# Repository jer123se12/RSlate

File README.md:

# RSlate
A 40key acrylic stack keyboard that is either hotswap with low profile switches or normal one but not hotswap.
Supports Vial
Currently Done!
---
|||
|---|---|
|Front|Back|
---
3d files are at [here](https://cad.onshape.com/documents/8e13d1f4745863165f092818/w/d03652fcd09787199e2b8651/e/c43cd68ad85962de6582dd97)

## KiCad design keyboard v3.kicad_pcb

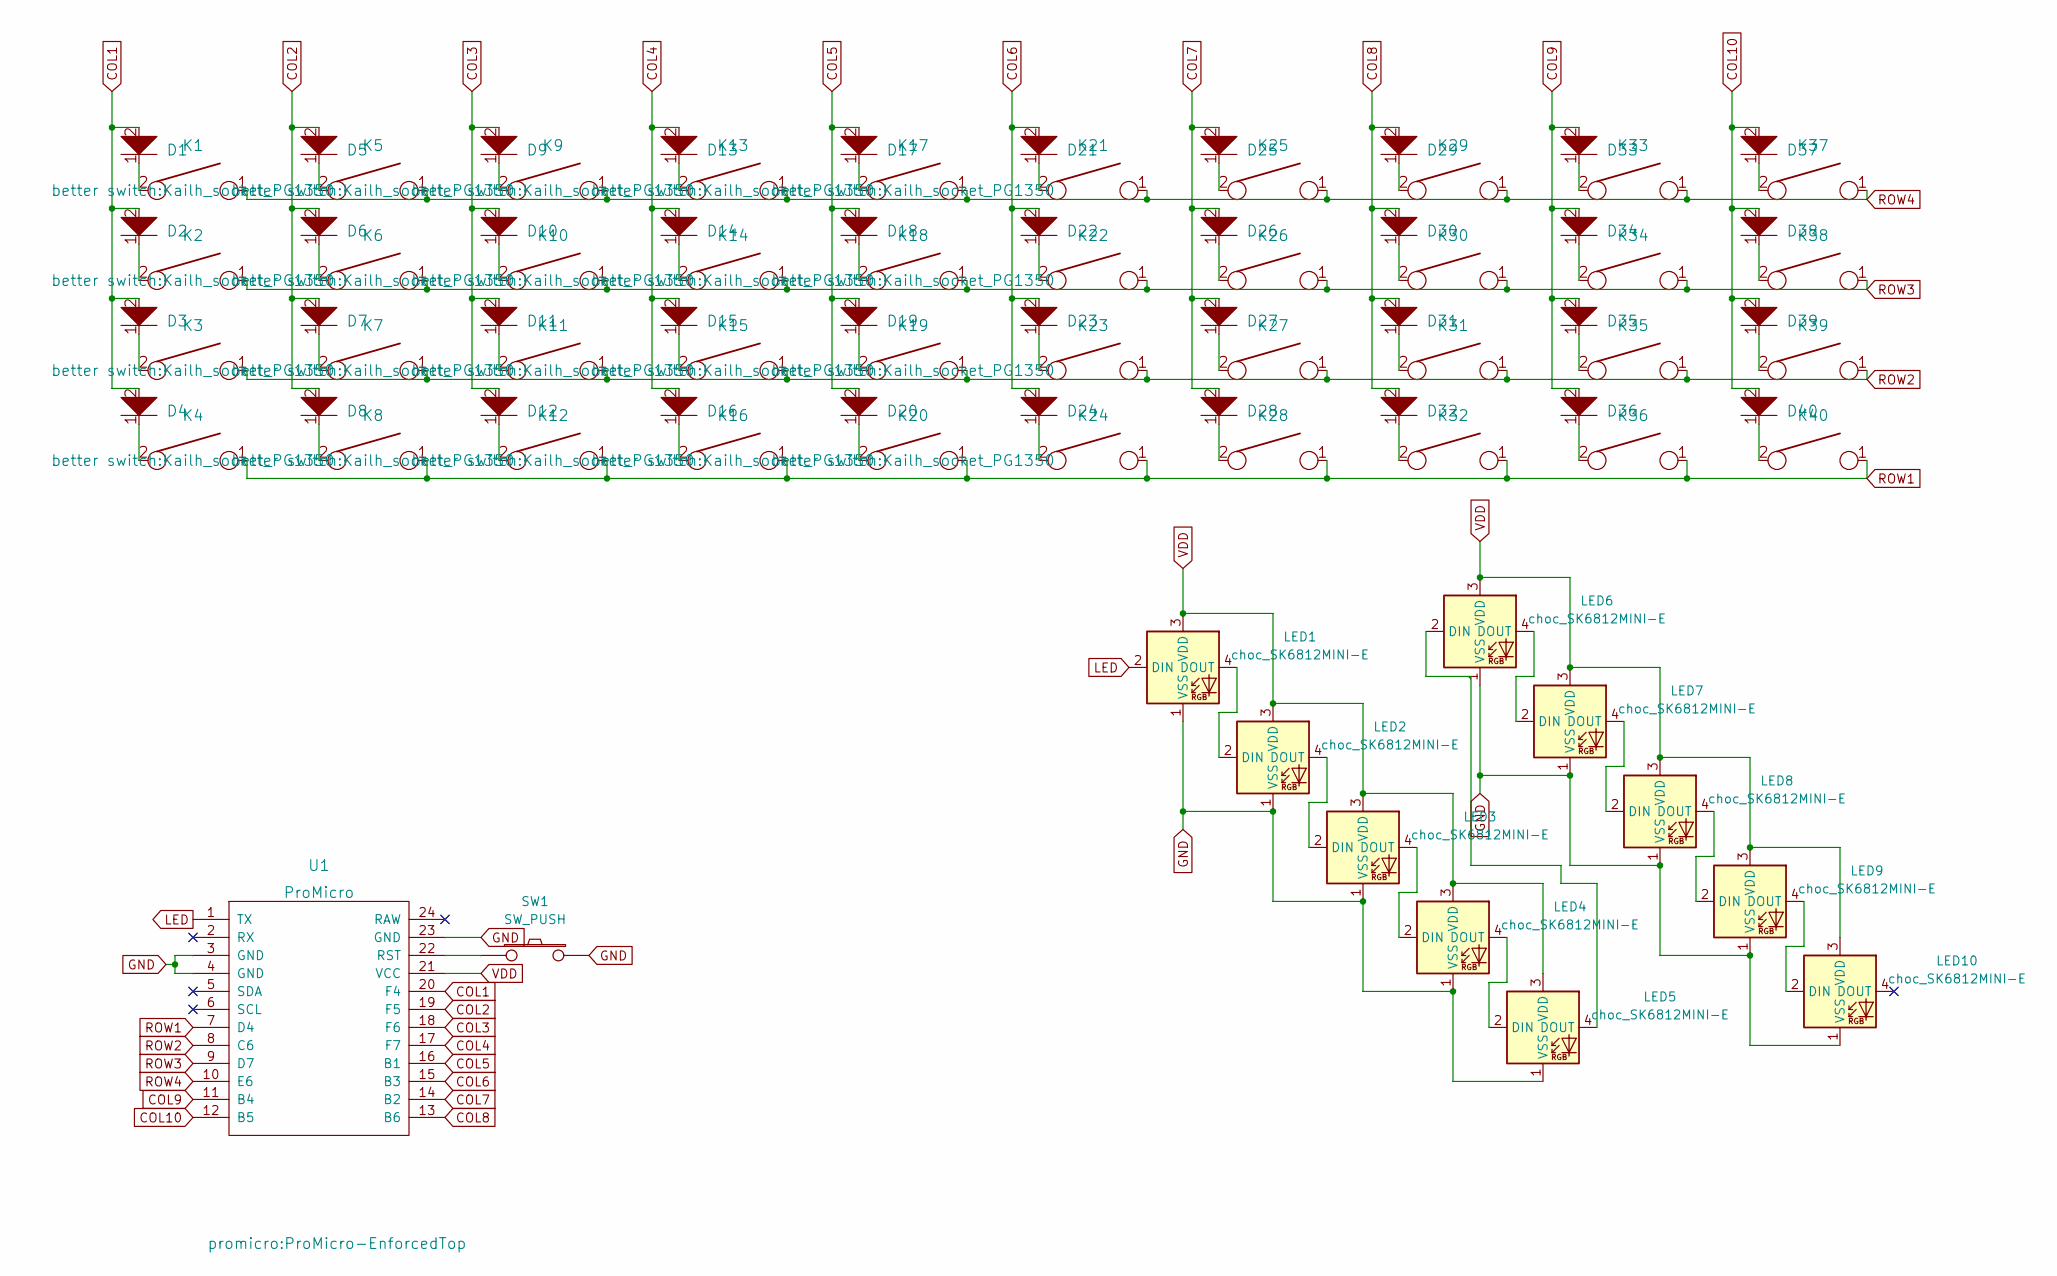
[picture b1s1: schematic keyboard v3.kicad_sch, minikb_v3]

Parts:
D1, D2, D3, D4, D5, D6, D7, D8, D9, D10, D11, D12, D13, D14, D15, D16, D17, D18, D19, D20, D21, D22, D23, D24, D25, D26, D27, D28, D29, D30, D31, D32, D33, D34, D35, D36, D37, D38, D39, D40: D; D_axial
K1, K2, K3, K4, K5, K6, K7, K8, K9, K10, K11, K12, K13, K14, K15, K16, K17, K18, K19, K20, K21, K22, K23, K24, K25, K26, K27, K28, K29, K30, K31, K32, K33, K34, K35, K36, K37, K38, K39, K40: KEYSW; Kailh_socket_PG1350
LED1, LED2, LED3, LED4, LED5, LED6, LED7, LED8, LED9, LED10: choc_SK6812MINI-E; LED_SK6812_PLCC4_5.0x5.0mm_P3.2mm
SW1: SW_PUSH; SW_PUSH_6mm
U1: ProMicro; ProMicro-EnforcedTop

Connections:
COL1: D1.2, D2.2, D3.2, D4.2, U1.20 (F4)
COL2: D5.2, D6.2, D7.2, D8.2, U1.19 (F5)
COL3: D9.2, D10.2, D11.2, D12.2, U1.18 (F6)
COL4: D13.2, D14.2, D15.2, D16.2, U1.17 (F7)
COL5: D17.2, D18.2, D19.2, D20.2, U1.16 (B1)
COL6: D21.2, D22.2, D23.2, D24.2, U1.15 (B3)
COL7: D25.2, D26.2, D27.2, D28.2, U1.14 (B2)
COL8: D29.2, D30.2, D31.2, D32.2, U1.13 (B6)
COL9: D33.2, D34.2, D35.2, D36.2, U1.11 (B4)
COL10: D37.2, D38.2, D39.2, D40.2, U1.12 (B5)
GND: LED1.1 (VSS), LED2.1 (VSS), LED3.1 (VSS), LED4.1 (VSS), LED5.1 (VSS), LED6.1 (VSS), LED7.1 (VSS), LED8.1 (VSS), LED9.1 (VSS), LED10.1 (VSS), SW1.2, U1.3 (GND), U1.4 (GND), U1.23 (GND)
LED: LED1.2 (DIN), U1.1 (TX)
unnamed: D1.1, K1.2
unnamed: D2.1, K2.2
unnamed: D3.1, K3.2
unnamed: D4.1, K4.2
unnamed: D5.1, K5.2
unnamed: D6.1, K6.2
unnamed: D7.1, K7.2
unnamed: D8.1, K8.2
unnamed: D9.1, K9.2
unnamed: D10.1, K10.2
unnamed: D11.1, K11.2
unnamed: D12.1, K12.2
unnamed: D13.1, K13.2
unnamed: D14.1, K14.2
unnamed: D15.1, K15.2
unnamed: D16.1, K16.2
unnamed: D17.1, K17.2
unnamed: D18.1, K18.2
unnamed: D19.1, K19.2
unnamed: D20.1, K20.2
unnamed: D21.1, K21.2
unnamed: D22.1, K22.2
unnamed: D23.1, K23.2
unnamed: D24.1, K24.2
unnamed: D25.1, K25.2
unnamed: D26.1, K26.2
unnamed: D27.1, K27.2
unnamed: D28.1, K28.2
unnamed: D29.1, K29.2
unnamed: D30.1, K30.2
unnamed: D31.1, K31.2
unnamed: D32.1, K32.2
unnamed: D33.1, K33.2
unnamed: D34.1, K34.2
unnamed: D35.1, K35.2
unnamed: D36.1, K36.2
unnamed: D37.1, K37.2
unnamed: D38.1, K38.2
unnamed: D39.1, K39.2
unnamed: D40.1, K40.2
unnamed: LED1.4 (DOUT), LED2.2 (DIN)
unnamed: LED2.4 (DOUT), LED3.2 (DIN)
unnamed: LED3.4 (DOUT), LED4.2 (DIN)
unnamed: LED4.4 (DOUT), LED5.2 (DIN)
unnamed: LED5.4 (DOUT), LED6.2 (DIN)
unnamed: LED6.4 (DOUT), LED7.2 (DIN)
unnamed: LED7.4 (DOUT), LED8.2 (DIN)
unnamed: LED8.4 (DOUT), LED9.2 (DIN)
unnamed: LED9.4 (DOUT), LED10.2 (DIN)
unnamed: SW1.1, U1.22 (RST)
ROW1: K4.1, K8.1, K12.1, K16.1, K20.1, K24.1, K28.1, K32.1, K36.1, K40.1, U1.7 (D4)
ROW2: K3.1, K7.1, K11.1, K15.1, K19.1, K23.1, K27.1, K31.1, K35.1, K39.1, U1.8 (C6)
ROW3: K2.1, K6.1, K10.1, K14.1, K18.1, K22.1, K26.1, K30.1, K34.1, K38.1, U1.9 (D7)
ROW4: K1.1, K5.1, K9.1, K13.1, K17.1, K21.1, K25.1, K29.1, K33.1, K37.1, U1.10 (E6)
VDD: LED1.3 (VDD), LED2.3 (VDD), LED3.3 (VDD), LED4.3 (VDD), LED5.3 (VDD), LED6.3 (VDD), LED7.3 (VDD), LED8.3 (VDD), LED9.3 (VDD), LED10.3 (VDD), U1.21 (VCC)

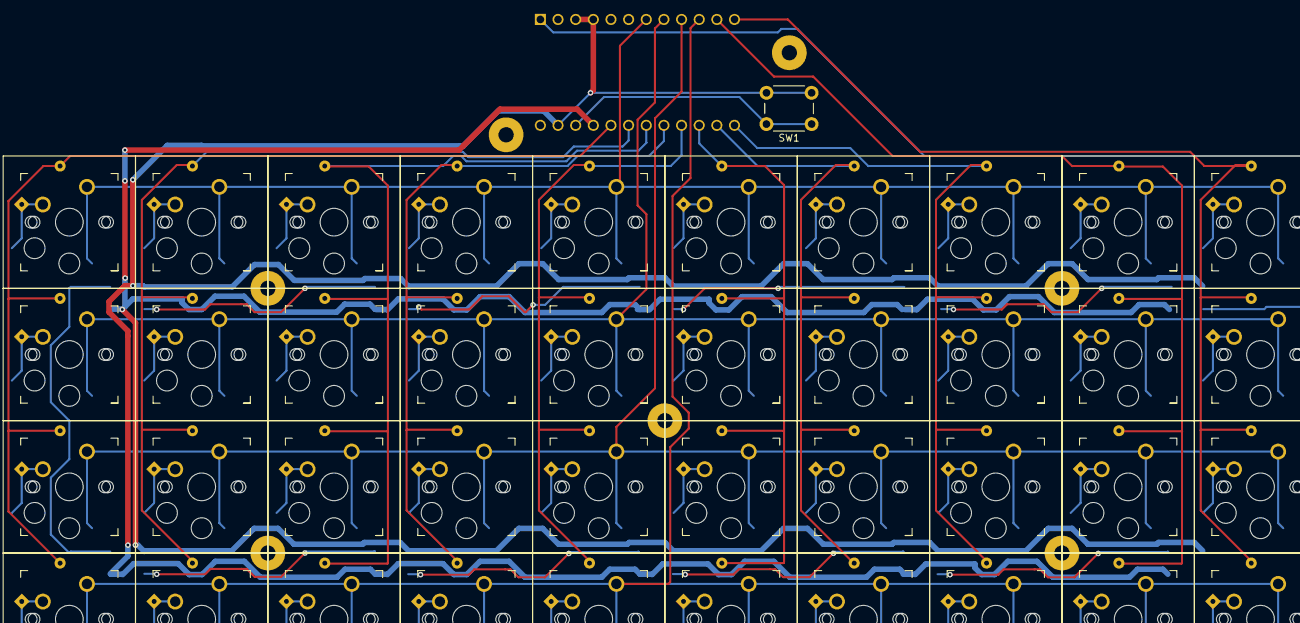
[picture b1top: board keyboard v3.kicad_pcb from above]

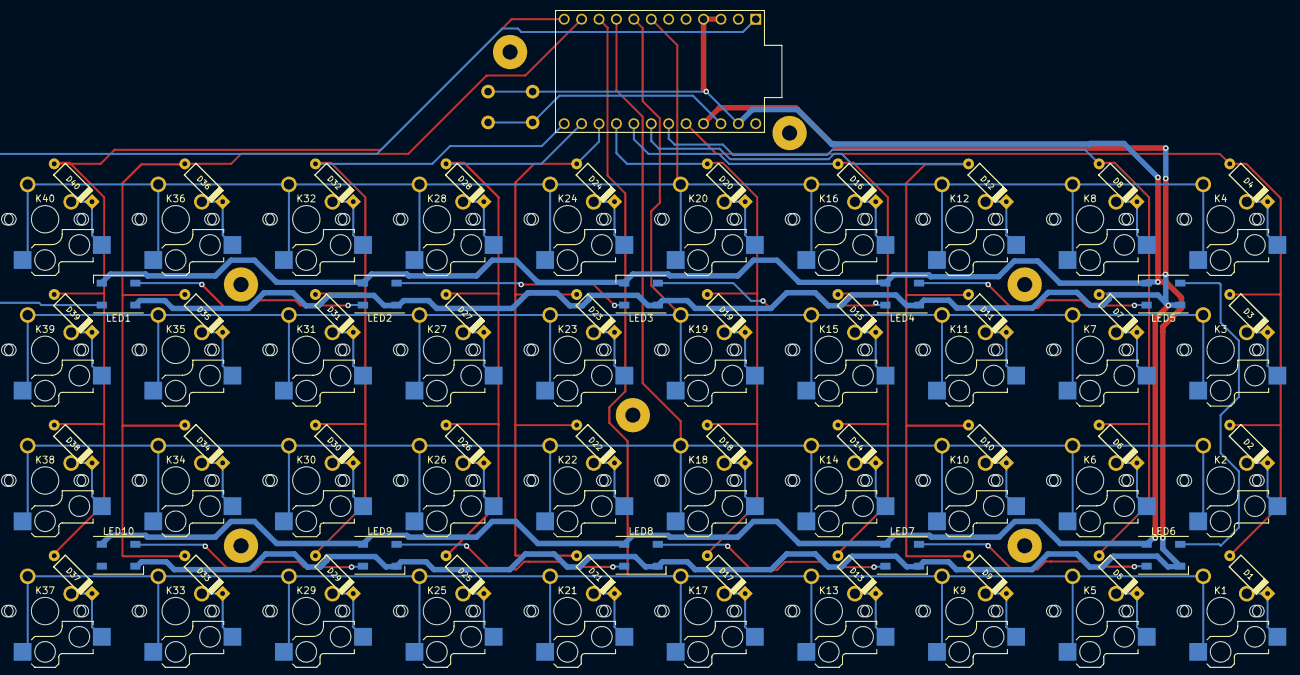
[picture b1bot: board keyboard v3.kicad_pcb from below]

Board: 2 copper layers, 99 parts (51 on the bottom side), 67 nets.

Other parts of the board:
H1, H1#2, H1#3, H1#4, H1#5, H1#6, H1#7: M2; MountingHole_M2

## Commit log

2022-09-22 nice
2022-10-13 files!
2022-11-03 artsey
